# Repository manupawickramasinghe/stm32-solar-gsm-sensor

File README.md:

# stm32-solar-gsm-sensor
Firmware and hardware guide for an open-source, solar-powered agricultural sensor system based on the STM32 "Blue Pill" and a SIM800L GSM module.

This project is designed for remote environmental monitoring. It periodically reads data from multiple sensors based on DIP switch configuration, aggregates the data, and sends a summary report via SMS to a predefined list of phone numbers. It is optimized for low-power operation, making it suitable for solar or battery-powered deployments.

## Features
- **Multi-Sensor Support with DIP Switch Selection**: 
  - DHT11 temperature and humidity sensor
  - DS18B20 waterproof temperature sensor
  - FC-28 soil moisture sensor
  - MQ2 gas sensor
  - 4-position DIP switch for enabling/disabling individual sensors

- **GSM Connectivity**: Uses a SIM800L module to connect to the cellular network for sending and receiving SMS messages.

- **Periodic Data Reporting**: The device wakes up every 5 minutes to take sensor readings from enabled sensors only.

- **Dynamic SMS Content**: SMS reports include only data from sensors that are enabled via DIP switches. If no sensors are enabled, only timestamp is sent.

- **Averaged Data SMS**: After a set number of readings (e.g., 12 readings over 60 minutes), it calculates the average sensor values and sends a consolidated report via SMS.

- **Multi-Recipient SMS**: Sends the report to a configurable list of multiple phone numbers.

- **Network Timestamp**: Fetches the current date and time from the cellular network and includes it in every SMS report for accurate logging.

- **Persistent Counter**: Uses Flash memory emulation (since the STM32F103C8T6 does not have built-in EEPROM) to save its reading counter, ensuring it can resume its cycle even after a power loss or reset.

- **Remote Control via SMS**: Comprehensive SMS command system for remote configuration and monitoring.

## Hardware Requirements
- **Microcontroller**: STM32F103C8T6 "Blue Pill" board.

- **GSM Module**: SIM800L module (ensure it comes with a spring antenna and a valid 2G SIM card).

- **DIP Switch**: 4-position DIP switch for sensor selection.

- **Sensors**:
  - DHT11 Temperature and Humidity Sensor (Pin: PB1)
  - DS18B20 Waterproof Temperature Sensor (Pin: PB0) with 4.7kΩ pull-up resistor
  - FC-28 Soil Moisture Sensor (Analog Pin: PA1)
  - MQ2 Gas Sensor (Analog Pin: PA4)

- **Pin Assignments for DIP Switches**:
  - DIP Switch 1 (DHT11): PC13
  - DIP Switch 2 (DS18B20): PC14  
  - DIP Switch 3 (Soil Moisture): PC15
  - DIP Switch 4 (MQ2 Gas): PB12

- **Programmer**: FTDI FT232RL USB-to-Serial adapter for flashing the firmware.

- **Power Supply**:
  - A stable power source for the SIM800L is critical. A 3.7V LiPo battery or a dedicated buck converter capable of supplying at least 2A peak current is highly recommended. Powering the SIM800L directly from the Blue Pill's 3.3V pin will cause instability.

## Software & Setup (Arduino IDE)
This project is built using the Arduino IDE with the official STM32 core.

1. **Install Arduino IDE**
   If you don't have it, download and install the latest version of the Arduino IDE.

2. **Install STM32 Board Support**
   Open the Arduino IDE.

   Go to `File > Preferences`.

   In the "Additional boards manager URLs" field, paste the following URL:

   ```
   https://github.com/stm32duino/BoardManagerFiles/raw/main/package_stmicroelectronics_index.json
   ```

   Go to `Tools > Board > Boards Manager...`.

   Search for "STM32 MCU based boards" and install the package by STMicroelectronics.

3. **Install Required Libraries**
   You need to install three libraries for the sensors.

   Go to `Tools > Manage Libraries...`.

   Search for and install each of the following libraries:

   - DHT sensor library by Adafruit

   - OneWire by Paul Stoffregen

   - DallasTemperature by Miles Burton

4. **Configure the Code**
   Open the `.ino` sketch file in the Arduino IDE.

   Modify the `phoneNumbers` array to include the recipient phone numbers you want to send the SMS reports to. Make sure to use the international format (e.g., +94...).

   ```cpp
   String phoneNumbers[] = {"+94719593248", "+94719751003"};
   ```

## Flashing the Firmware (Manual Upload)
Since this project uses an FTDI adapter, you cannot use the standard "Upload" button in the Arduino IDE. You must compile the binary and flash it manually using a command-line tool.

### Step 1: Compile and Export the Binary
In the Arduino IDE, select the correct board settings:

- `Tools > Board: "STM32 MCU based boards" > "Generic STM32F1 series"`

- `Tools > Board part number: "Bluepill F103C8"`

- `Tools > Upload method: "STM32CubeProgrammer (Serial)"`

Go to `Sketch > Export compiled Binary`. This will compile your code and create a `.hex` and `.bin` file in the sketch folder.

### Step 2: Install stm32flash
This is a lightweight, reliable tool for flashing STM32 devices via UART.

Open a terminal on your Linux machine and run:

```bash
sudo apt update
sudo apt install stm32flash
```

### Step 3: Set Up Hardware for Flashing
This is the most critical part. You must put the STM32 into its hardware bootloader mode.

- **Set Jumpers**:

  - Set the `BOOT0` jumper to the '1' position (HIGH).

  - Set the `BOOT1` jumper to the '0' position (LOW).

- **Wire the FTDI Adapter**:

  - FTDI GND -> STM32 GND

  - FTDI TX -> STM32 PA10 (RX1)

  - FTDI RX -> STM32 PA9 (TX1)

- **Connect and Reset**: Connect the FTDI adapter to your computer. Now, press the RESET button on the Blue Pill board. The board is now waiting for programming commands.

### Step 4: Fix Serial Port Permissions (One-Time Setup)
On Linux, your user needs permission to access serial devices.

Add your user to the dialout group:

```bash
sudo usermod -a -G dialout $USER
```

IMPORTANT: For this change to take effect, you must log out and log back in or reboot your computer.

### Step 5: Flash the Firmware
Open a terminal and navigate to your Arduino sketch directory where the `.bin` file was exported.

Run the `stm32flash` command:

```bash
stm32flash -b 115200 -w YourSketchName.ino.bin -v -g 0x0 /dev/ttyUSB0
```

- `-b 115200`: Sets the baud rate for reliable communication.

- `-w YourSketchName.ino.bin`: Specifies the binary file to write.

- `-v`: Verifies the flash after writing.

- `-g 0x0`: Starts execution from the beginning of the flash memory after programming.

- `/dev/ttyUSB0`: The serial port of your FTDI adapter.

### Step 6: Run the Application
Disconnect the power.

Set the `BOOT0` jumper back to the '0' position.

Reconnect power or press the RESET button.

The board will now boot into your application. You can open the Arduino IDE's Serial Monitor at 9600 baud to see the debug output.

## Code Explanation
- **Configuration (`#define`)**: All hardware pins, timing delays, and operational thresholds are defined at the top of the file for easy configuration.

- **setup()**: This function runs once on startup. It initializes the serial ports for debugging, starts the DHT and DS18B20 sensors, and crucially, initializes the SIM800L module with a series of AT commands to prepare it for sending SMS. It also reads the last known `smsCounter` value from the EEPROM.

- **loop()**: This is the main operational cycle.

  - It first ensures the GSM module is initialized and ready.

  - It reads the current temperature and humidity from both sensors.

  - The readings are added to summing variables (`dhtHumSum`, `dhtTempSum`, etc.).

  - A counter (`smsCounter`) is incremented and saved to the EEPROM.

  - It checks if `smsCounter` has reached the `SMS_SEND_THRESHOLD` (e.g., 12).

  - If the threshold is met, it calculates the averages, fetches a network timestamp, formats the SMS message, and sends it to all phone numbers in the `phoneNumbers` array.

  - Finally, it resets the summing variables and the `smsCounter` back to zero and waits for 5 minutes (`MAIN_LOOP_CYCLE_DELAY`) before starting the next cycle.

- **GSM Helper Functions**: Functions like `sendSMS()`, `getGsmTimestamp()`, and `handleSim800lInput()` abstract the complexity of communicating with the SIM800L module.

## DIP Switch Configuration
The system uses a 5-position DIP switch to enable/disable individual sensors and MQTT publishing:

- **DIP Switch 1 (PC13)**: DHT11 Temperature & Humidity Sensor
- **DIP Switch 2 (PC14)**: DS18B20 Waterproof Temperature Sensor  
- **DIP Switch 3 (PC15)**: FC-28 Soil Moisture Sensor
- **DIP Switch 4 (PB12)**: MQ2 Gas Sensor
- **DIP Switch 5 (PB13)**: MQTT Publishing to test.mosquitto.org

**Switch Logic**: 
- Switch DOWN (pulled to ground) = Feature ENABLED
- Switch UP (pulled high) = Feature DISABLED

**Important**: The system reads DIP switches only during startup/boot. To change sensor or MQTT configuration, modify the DIP switches and restart the system. Only enabled sensors are read and included in SMS reports. If MQTT is enabled, data will be published to test.mosquitto.org after SMS transmission.

## SMS Commands
The system supports remote configuration and monitoring via SMS commands. Send these commands to the SIM card phone number:

### Configuration Commands
- **`NUMSETA +1234567890`**: Set phone number A
- **`NUMSETB +1234567890`**: Set phone number B  
- **`NUMSETC +1234567890`**: Set phone number C
- **`SETID 12345`**: Set customer ID (max 9 characters)

### Status Commands
- **`STATUS`**: Get current configuration, enabled sensors, and MQTT status
- **`TEST`**: Simple connectivity test
- **`SENSOR`**: Get current real-time sensor readings from enabled sensors
- **`MQTT`**: Test MQTT publishing (if MQTT enabled)

### Example SMS Responses
- **STATUS**: `ID:12345 A:+94719593248 B:+94719751003 C:+94768378406 Sensors: DHT DS18B20 SOIL MQTT`
- **SENSOR**: `ID:12345 Current: DHT H:65.2% T:28.4C; DS18B20:27.8C; Soil:45.3%;`
- **MQTT**: `ID:12345 MQTT test publish initiated`

## MQTT Integration
When the MQTT DIP switch is enabled (DIP Switch 5), the system will:

1. **Automatic Publishing**: After sending SMS data, automatically publish sensor data to MQTT
2. **MQTT Broker**: Uses test.mosquitto.org on port 1883 (public test broker)
3. **Topic Structure**: `sensors/stm32/{customer_id}`
4. **Data Format**: JSON payload with sensor readings and metadata
5. **Manual Testing**: Use `MQTT` SMS command to test publishing

### MQTT Data Example
```json
{
  "customer_id": "FARM01",
  "timestamp": "2025-08-03 14:30:15",
  "dht_humidity": 65.2,
  "dht_temperature": 28.4,
  "ds18b20_temperature": 27.8,
  "soil_moisture": 45.3,
  "gas_level": 12.1,
  "reading_count": 12
}
```

All configurations are saved to EEPROM and persist across power cycles.

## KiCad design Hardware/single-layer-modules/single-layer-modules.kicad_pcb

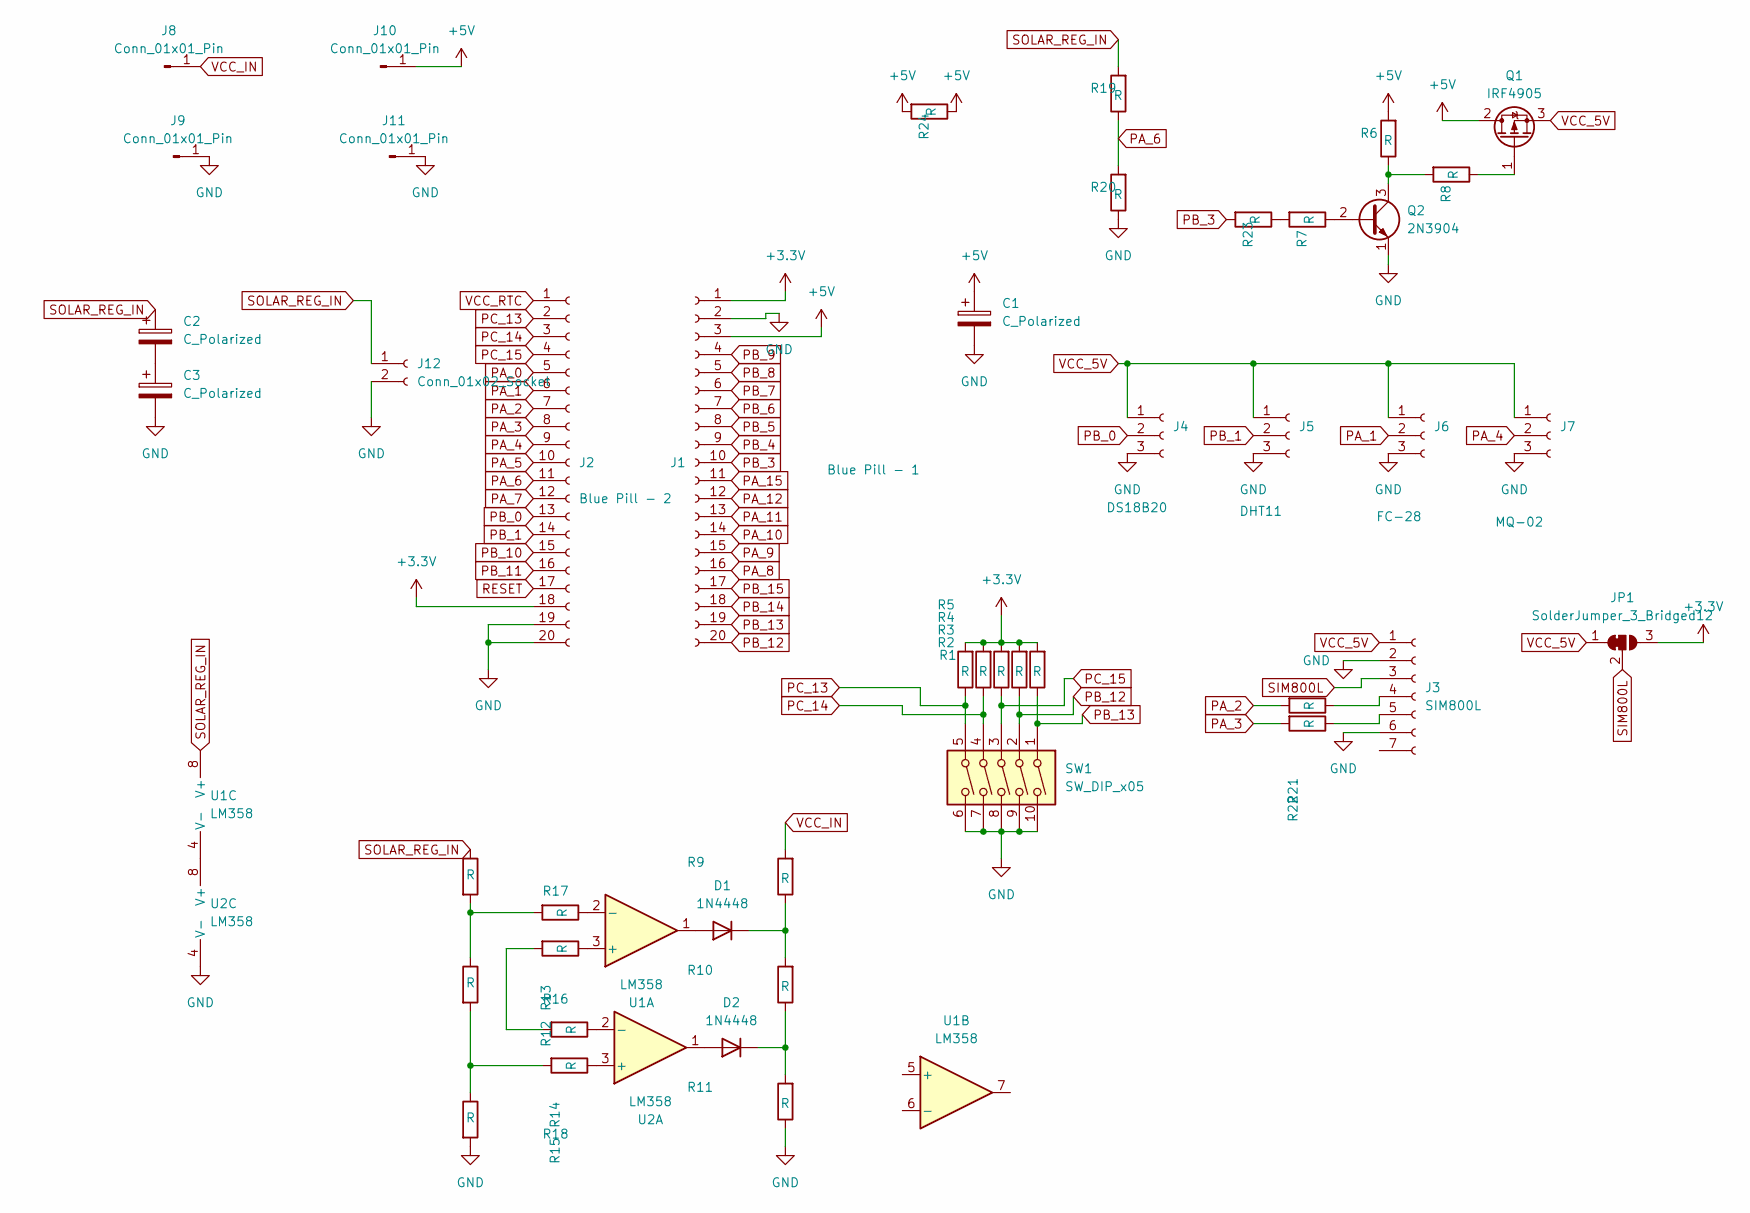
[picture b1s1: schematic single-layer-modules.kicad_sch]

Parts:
C1, C2, C3: C_Polarized; CP_Radial_D17.0mm_P7.50mm
D1, D2: 1N4448; D_DO-35_SOD27_P7.62mm_Horizontal
J1: Blue Pill - 1; PinHeader_1x20_P2.54mm_Vertical
J2: Blue Pill - 2; PinHeader_1x20_P2.54mm_Vertical
J3: SIM800L; PinSocket_1x07_P2.54mm_Vertical
J4: DS18B20; PinSocket_1x03_P2.54mm_Vertical
J5: DHT11; PinSocket_1x03_P2.54mm_Vertical
J6: FC-28; PinSocket_1x03_P2.54mm_Vertical
J7: MQ-02; PinSocket_1x03_P2.54mm_Vertical
J8, J9, J10, J11: Conn_01x01_Pin; PinSocket_1x01_P2.54mm_Vertical
J12: Conn_01x02_Socket; AMASS_XT30UPB-M_1x02_P5.0mm_Vertical
JP1: SolderJumper_3_Bridged12; JST_PH_S3B-PH-K_1x03_P2.00mm_Horizontal
Q1: IRF4905; TO-220-3_Vertical
Q2: 2N3904; TO-92L_HandSolder
R1, R2, R3, R4, R5, R6, R7, R8, R9, R10, R11, R12, R13, R14, R15, R16, R17, R18, R19, R20, R21, R22, R23, R24: R; R_Axial_DIN0411_L9.9mm_D3.6mm_P15.24mm_Horizontal
SW1: SW_DIP_x05; SW_DIP_SPSTx05_Slide_9.78x14.88mm_W7.62mm_P2.54mm
U1, U2: LM358; DIP-8_W7.62mm_LongPads

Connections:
+3.3V: J1.1, J2.18, JP1.3 (B), R1.2, R2.2, R3.2, R4.2, R5.2
+5V: C1.1, J1.3, J10.1, Q1.2 (D), R6.2, R24.1, R24.2
GND: C1.2, C3.2, J1.2, J2.19, J2.20, J3.2, J3.6, J4.3, J5.3, J6.3, J7.3, J8.3, J9.1, J11.1, J12.2, Q2.1 (E), R11.1, R18.2, R20.1, SW1.6, SW1.7, SW1.8, SW1.9, SW1.10, U2.4 (V-)
unnamed: C2.2, C3.1
unnamed: D1.2 (A), U1.1
unnamed: D1.1 (K), R9.1, R10.2
unnamed: D2.2 (A), U2.1
unnamed: D2.1 (K), R10.1, R11.2
unnamed: J3.4, R21.1
unnamed: J3.5, R22.1
unnamed: Q1.1 (G), R8.1
unnamed: Q2.2 (B), R7.1
unnamed: Q2.3 (C), R6.1, R8.2
unnamed: R12.2, R14.2
unnamed: R13.2, R16.1, R17.2
unnamed: R15.2, R16.2, R18.1
unnamed: R7.2, R23.1
unnamed: R12.1, U1.3 (+)
unnamed: R13.1, U1.2 (-)
unnamed: U1.4 (V-), U2.8 (V+)
unnamed: R15.1, U2.3 (+)
unnamed: R14.1, U2.2 (-)
PA_0: J2.5
PA_1: J2.6, J6.2
PA_2: J2.7, R21.2
PA_3: J2.8, R22.2
PA_4: J2.9, J7.2
PA_5: J2.10
PA_6: J2.11, R19.1, R20.2
PA_7: J2.12
PA_8: J1.16
PA_9: J1.15
PA_10: J1.14
PA_11: J1.13
PA_12: J1.12
PA_15: J1.11
PB_0: J2.13, J4.2
PB_1: J2.14, J5.2
PB_3: J1.10, R23.2
PB_4: J1.9
PB_5: J1.8
PB_6: J1.7
PB_7: J1.6
PB_8: J1.5
PB_9: J1.4
PB_10: J2.15
PB_11: J2.16
PB_12: J1.20, R2.1, SW1.2
PB_13: J1.19, R1.1, SW1.1
PB_14: J1.18
PB_15: J1.17
PC_13: J2.2, R5.1, SW1.5
PC_14: J2.3, R4.1, SW1.4
PC_15: J2.4, R3.1, SW1.3
RESET: J2.17
SIM800L: J3.3, JP1.2 (C)
SOLAR_REG_IN: C2.1, J12.1, R17.1, R19.2, U1.8 (V+)
VCC_RTC: J2.1

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
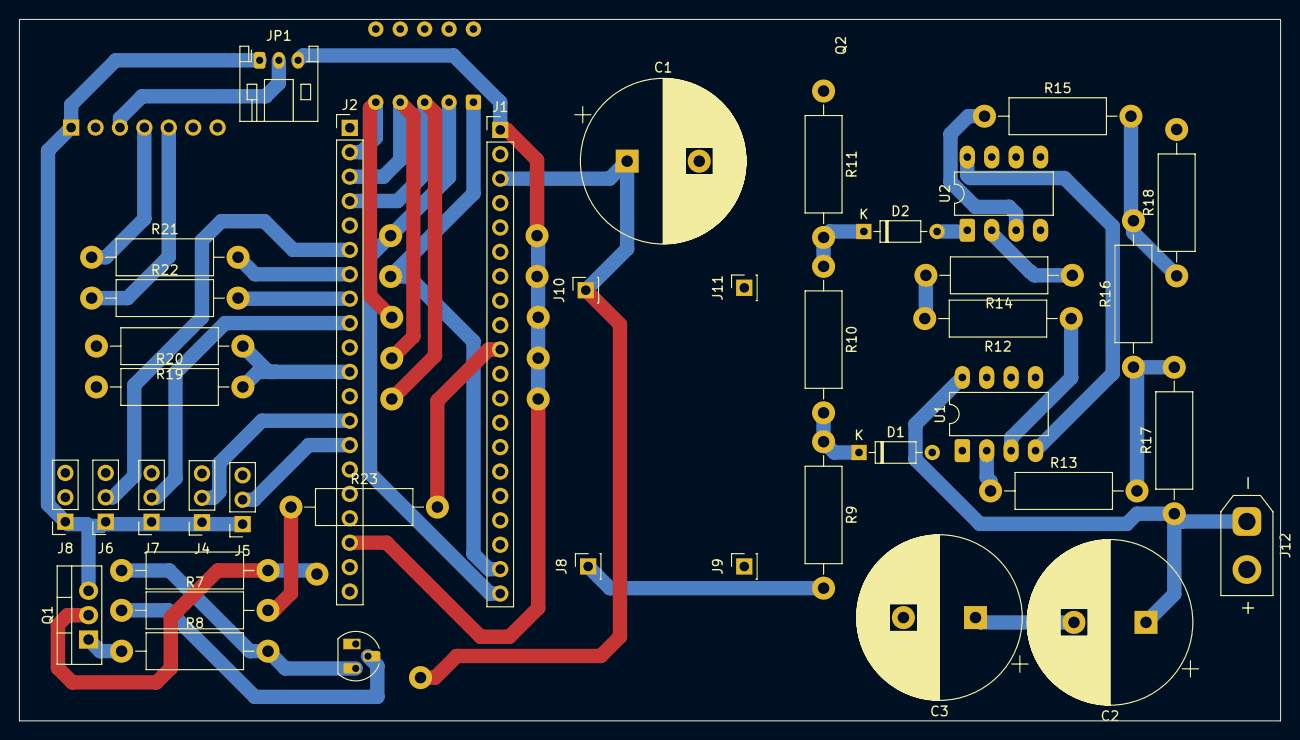
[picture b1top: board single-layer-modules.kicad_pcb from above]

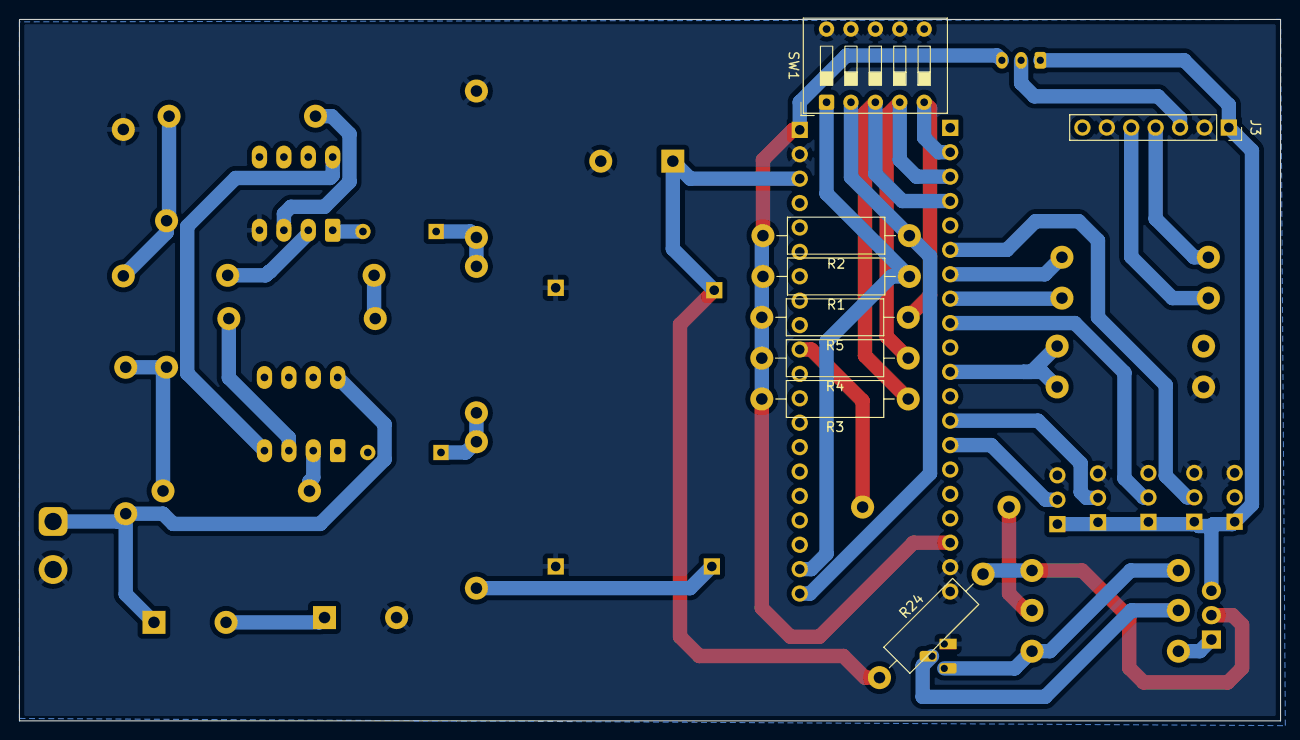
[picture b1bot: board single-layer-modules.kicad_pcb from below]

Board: 2 copper layers, 131.2 x 73.0 mm, 48 parts (8 on the bottom side), 39 nets.

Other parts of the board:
J8#2: Conn_01x01_Pin; PinSocket_1x01_P2.54mm_Vertical

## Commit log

2025-07-21 Refactor GSM module initialization and delay handling; replace magic numbers with defined constants for better readability and maintainability.
2025-07-21 Add initial files for single-layer modules design
    - Created new KiCad PCB file: single-layer-modules.kicad_pcb
    - Added project settings and configurations in single-layer-modules.kicad_prl
    - Established board design parameters in single-layer-modules.kicad_pro
    - Introduced schematic file: single-layer-modules.kicad_sch
    - Added lock file for schematic: ~single-layer-modules.kicad_sch.lck
    - Included backup zip file for single-layer modules
2025-07-29 Refactor GSM module initialization and sensor reading logic; add timestamp to SMS messages
2025-07-29 Refactor code structure for improved readability and maintainability
2025-07-29 Enhance GSM module functionality: refactor initialization, add timestamp support, and implement SMS sending with multiple recipients.
2025-07-29 Refactor GSM module logic: implement EEPROM for SMS counter, remove ADC condition checks, and streamline initialization process.
2025-07-29 Update README.md: Enhance project description, features, hardware requirements, and setup instructions for clarity and completeness.
2025-07-29 Update README.md: Clarify description of the sensor system and correct EEPROM usage details for persistent counter.
2025-07-29 Refactor main loop to implement state machine for sensor readings and data processing; remove ADC condition checks and streamline GSM initialization logic.
2025-07-29 Refactor GSM module: add function declarations, streamline variable scope, and remove unnecessary EEPROM commits.
2025-07-29 Add GitHub Actions workflow for build and release process
2025-07-29 Update artifact upload action to v4 and add retention policy for 90 days
2025-07-29 Enhance Arduino CLI installation and library setup with verbose output and verification steps
2025-07-29 Update Arduino CLI configuration and installation steps for STM32 support
2025-07-29 Enhance STM32 core installation and library setup with verbose output and verification steps
2025-07-29 Refactor STM32 library installation steps for clarity and verification
2025-07-29 Update library installation commands for STM32 setup to use specific library names
2025-07-29 cHANGING dht11 lIBRARY
2025-07-29 dht11 CHANGES
2025-07-29 cHAGING vEERSION
2025-07-29 Changiong Artifact UPloading
2025-07-29 Update Cacheing Location
2025-07-29 Change the Cache Config
2025-07-29 Change Action to Create Releases
2025-07-29 Add legacy STM32 and Arduino soil moisture firmware
    Added STM32-based and Arduino-based soil moisture sensor firmware, including source code, documentation, and VSCode configuration files. These files provide low-power sensor node implementations with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
2025-08-02 Modularize SMS-STM32 firmware and add new modules
    Refactored the SMS-STM32 firmware into multiple modules for better organization and maintainability. Added new files: config.h for configuration constants, gsm_module for GSM operations, sensor_manag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
2025-08-02 Add EEPROM storage for phone numbers and customer ID; introduce SMS processing states
2025-08-02 Implement EEPROM configuration functions for phone numbers and customer ID; add SMS command processing capabilities
2025-08-02 Enhance SMS functionality and response handling; increase delays for GSM commands and improve error handling for SMS sending
2025-08-02 Add SMS processing timeout and improve response handling; enhance data reception logic
2025-08-02 Update README.md to enhance documentation; add system operation details, SMS command examples, and troubleshooting guidance
2025-08-02 Enhance sensor support and configuration; add DIP switch functionality for enabling/disabling sensors, update README for multi-sensor details and SMS command instructions
2025-08-02 Update README to clarify DIP switch reading behavior; specify that sensor configuration changes require a system restart
2025-08-02 Add MQTT support and update DIP switch configuration; enhance README with MQTT details and commands
2025-08-12 Refactor MQTT GPRS setup and publish flow
    Added new states for APN and GPRS activation in the MQTT operation state machine. Improved the GPRS setup sequence, including explicit APN configuration and activation steps. Refactored MQTT publish 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
2025-08-13 Add autosave and backup files for PCB project
    Added KiCad autosave and backup files for the single-layer-modules project, including .kicad_pcb, .kicad_sch, and backup zip archives. Updated main PCB and schematic files with recent changes. Lock f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
2025-08-23 Add New PCB
2025-08-24 Implement code changes to enhance functionality and improve performance
